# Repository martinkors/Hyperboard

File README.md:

# Hyperboard

A custom development board based on an STM32F479VIT6, used to test custom written drivers.

This board is only a prototype, there are many things that could be improved. It is not advised to follow the design of this board, but instead only use it as a very simplified reference board.

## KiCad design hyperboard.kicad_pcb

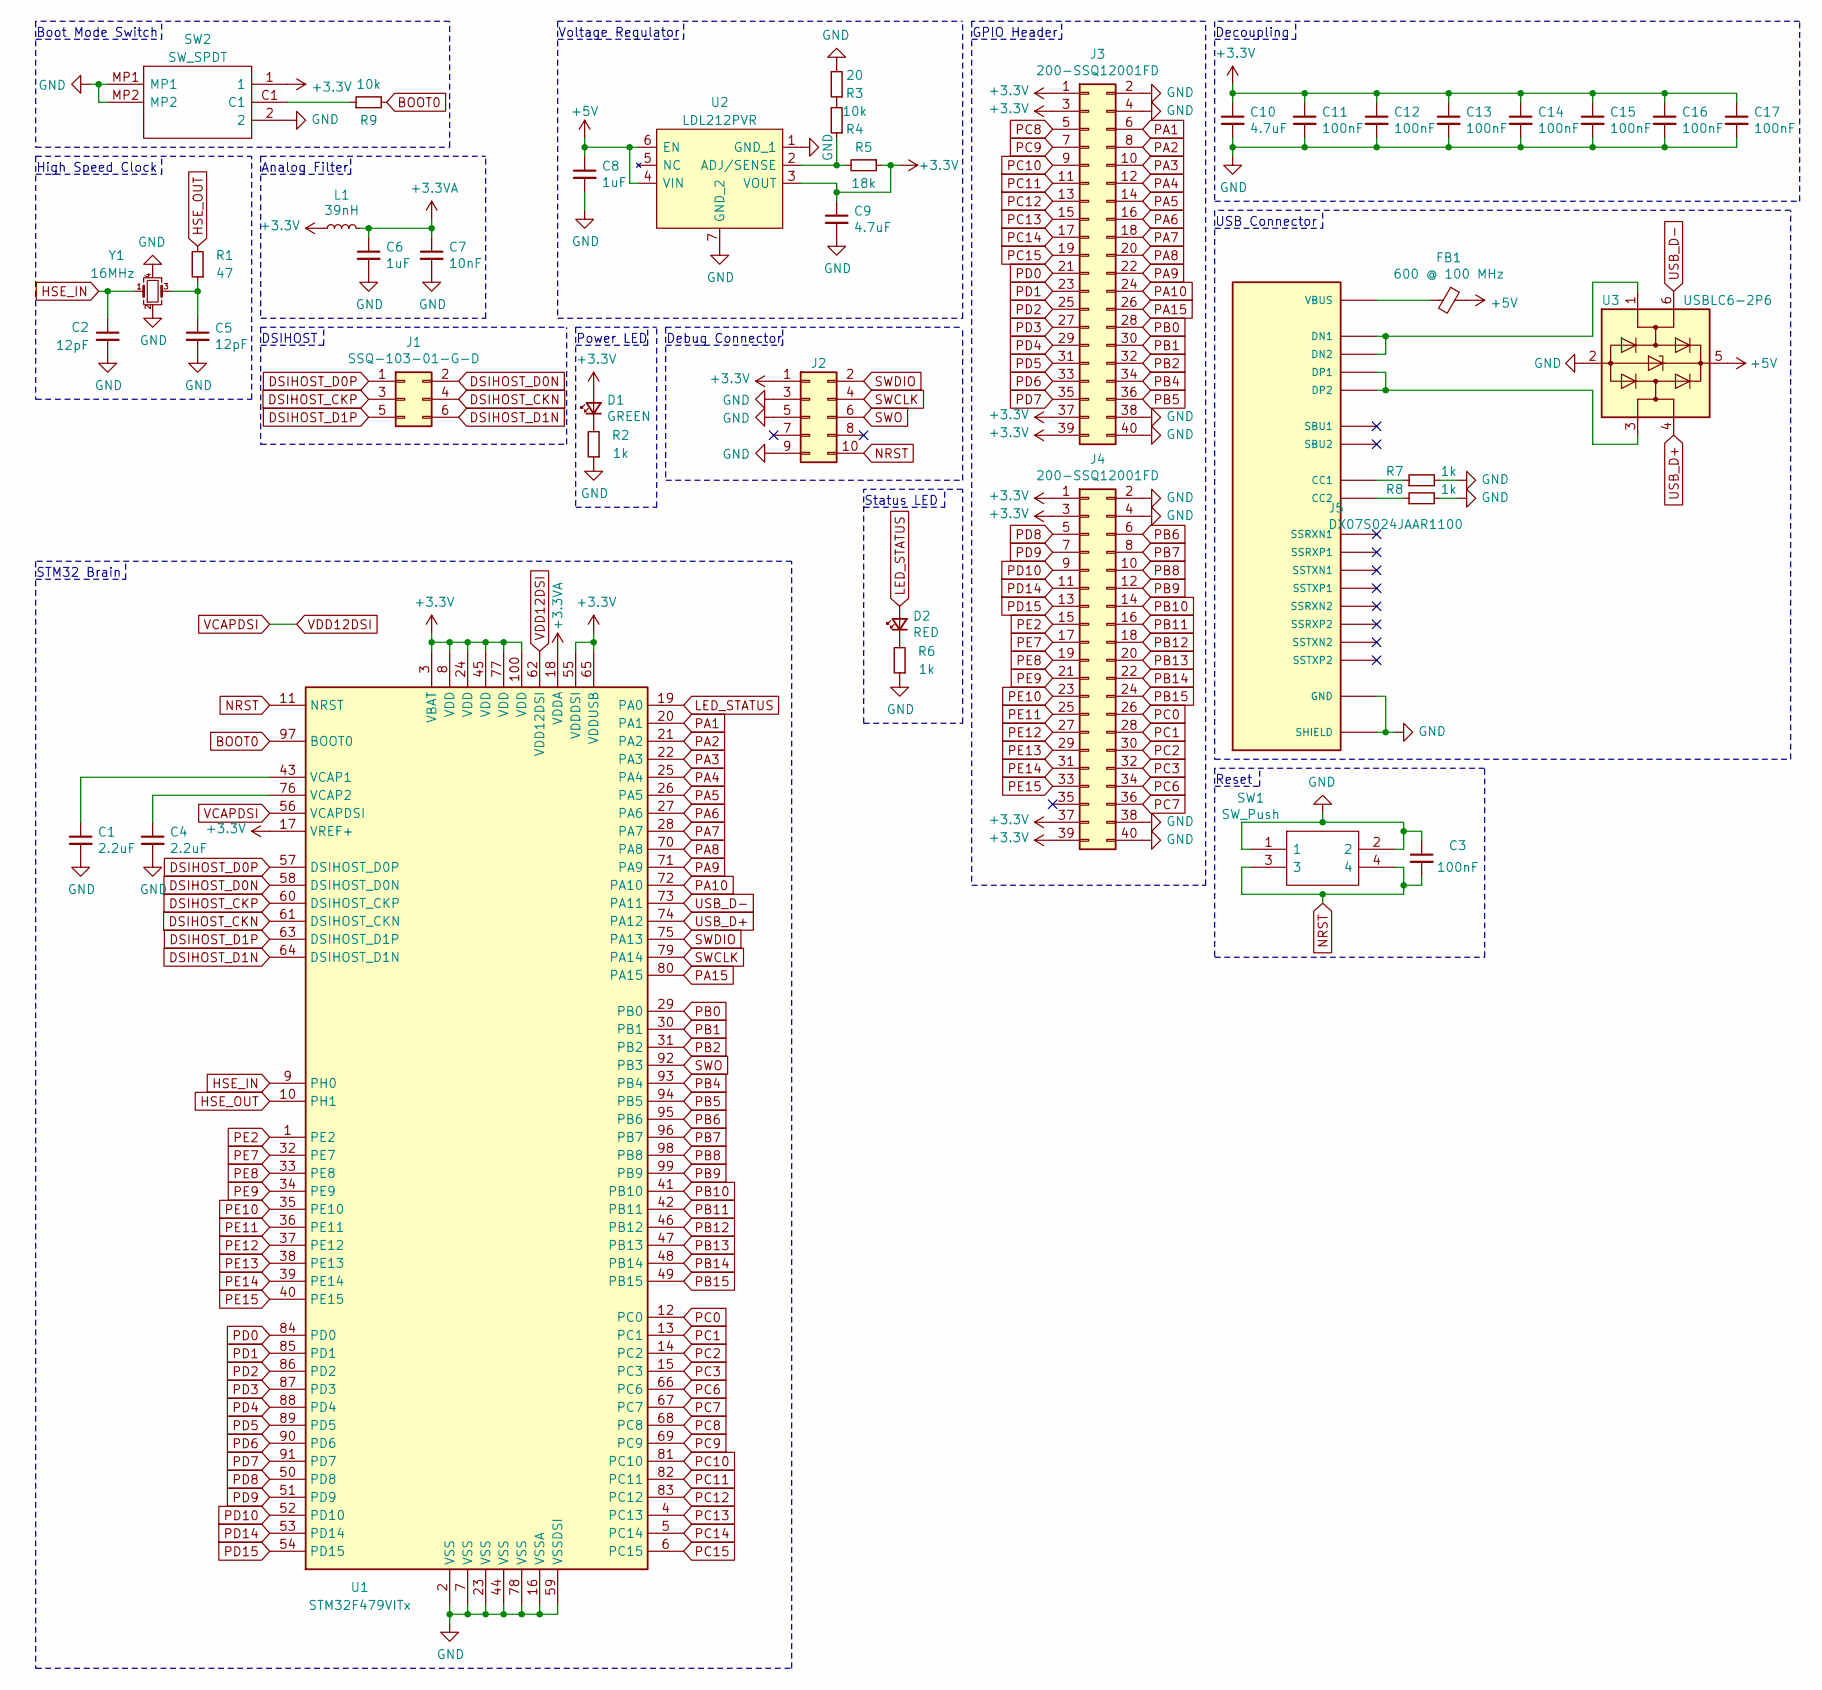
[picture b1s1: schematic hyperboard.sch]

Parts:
C1, C4: 2.2uF; C_0603_1608Metric; Mouser Part Number 187-CL10A225KA8NNNC; LCSC Part # C23630
C2, C5: 12pF; C_0603_1608Metric; Mouser Part Number 187-CL10C120JB81PNC; LCSC Part # C38523
C3, C11, C12, C13, C14, C15, C16, C17: 100nF; C_0402_1005Metric; Mouser Part Number 187-CL05B104KQ5NNNC; LCSC Part # C1525
C6: 1uF; C_0402_1005Metric; Mouser Part Number 187-CL05A105KQ5NNNC; LCSC Part # C52923
C7: 10nF; C_0402_1005Metric; Mouser Part Number 187-CL05B103JO5NNNC; LCSC Part # C15195
C8: 1uF; C_0402_1005Metric; Mouser Part Number 187-CL05A105KQ5NNNC; LCSC Part # C1525
C9: 4.7uF; C_0603_1608Metric; Mouser Part Number 187-CL10A475KQ8NNNC; LCSC Part # C1525
C10: 4.7uF; C_0603_1608Metric; Mouser Part Number 187-CL10A475KQ8NNNC; LCSC Part # C19666
D1: GREEN; LED_0805_2012Metric; Mouser Part Number 710-150080VS75000; LCSC Part # C188728
D2: RED; LED_0805_2012Metric; Mouser Part Number 710-150080RS75000; LCSC Part # C729289
FB1: 600 @ 100 MHz; L_0805_2012Metric; Mouser Part Number 710-742792040; LCSC Part # C1017
J1: SSQ-103-01-G-D; PinSocket_2x03_P2.54mm_Vertical; Mouser Part Number 200-SSQ10301GD
J2: FTSH-105-01-L-DV-K-TR; FTSH10501LDVKTR; Mouser Part Number 200-FTSH10501LDVKTR
J3, J4: 200-SSQ12001FD; SSQ-120-XX-YYY-D; Mouser Part Number 200-SSQ12001FD
J5: DX07S024JAAR1100; PARTREV 1.03; Mouser Part Number 656-DX07S024JAAR1100
L1: 39nH; L_0402_1005Metric; Mouser Part Number 710-7447840139; LCSC Part # C26443
R1: 47; R_0603_1608Metric; Mouser Part Number 667-ERJ-UP3J470V; LCSC Part # C23182
R2, R6, R7, R8: 1k; R_0603_1608Metric; Mouser Part Number 667-ERJ-UP3F1001V; LCSC Part # C21190
R3: 20; R_0603_1608Metric; Mouser Part Number 667-ERJ-UP3F20R0V; LCSC Part # C21190
R4: 10k; R_0603_1608Metric; Mouser Part Number 667-ERJ-UP3F1002V; LCSC Part # C22967
R5: 18k; R_0603_1608Metric; Mouser Part Number 667-ERJ-UP3F1802V; LCSC Part # C25804
R9: 10k; R_0603_1608Metric; Mouser Part Number 667-ERJ-UP3F1002V; LCSC Part # C25804
SW1: SW_Push; SKQGAKE010; Mouser Part Number 688-SKQGAKE010
SW2: SW_SPDT; JSX08001SAQNL; Mouser Part Number 688-SSAJ120100; LCSC Part # C319019
U1: STM32F479VITx; LQFP-100_14x14mm_P0.5mm; Mouser Part Number 511-STM32F479VIT6
U2: LDL212PVR; DFN-6-1EP_2x2mm_P0.65mm_EP1x1.6mm; Mouser Part Number 511-LDL212PVR; LCSC Part # C9056
U3: USBLC6-2P6; SOT-666; Mouser Part Number 511-USBLC6-2P6; LCSC Part # C7519
Y1: 16MHz; Crystal_SMD_3225-4Pin_3.2x2.5mm; Mouser Part Number 344-NX3225SA16MHZT1; LCSC Part # C13738

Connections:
+3.3VA: C6.1, C7.1, L1.2, U1.18 (VDDA)
+3V3: C9.1, C10.1, C11.1, C12.1, C13.1, C14.1, C15.1, C16.1, C17.1, D1.2 (A), J2.1, J3.1, J3.3, J3.37, J3.39, J4.1, J4.3, J4.37, J4.39, L1.1, R5.1, SW2.1, U1.3 (VBAT), U1.8 (VDD), U1.17 (VREF+), U1.24 (VDD), U1.45 (VDD), U1.55 (VDDDSI), U1.65 (VDDUSB), U1.77 (VDD), U1.100 (VDD), U2.3 (VOUT)
+5V: C8.1, FB1.1, U2.4 (VIN), U2.6 (EN), U3.5 (VBUS)
BOOT0: R9.2, U1.97 (BOOT0)
DSIHOST_CKN: J1.4, U1.61 (DSIHOST_CKN)
DSIHOST_CKP: J1.3, U1.60 (DSIHOST_CKP)
DSIHOST_D0N: J1.2, U1.58 (DSIHOST_D0N)
DSIHOST_D0P: J1.1, U1.57 (DSIHOST_D0P)
DSIHOST_D1N: J1.6, U1.64 (DSIHOST_D1N)
DSIHOST_D1P: J1.5, U1.63 (DSIHOST_D1P)
GND: C1.2, C2.2, C3.1, C4.2, C5.2, C6.2, C7.2, C8.2, C9.2, C10.2, C11.2, C12.2, C13.2, C14.2, C15.2, C16.2, C17.2, J2.3, J2.5, J2.9, J3.2, J3.4, J3.38, J3.40, J4.2, J4.4, J4.38, J4.40, J5.1 (SHIELD), J5.2 (SHIELD), J5.3 (SHIELD), J5.4 (SHIELD), J5.A1 (GND), J5.A12 (GND), J5.B1 (GND), J5.B12 (GND), R2.1, R3.2, R6.1, R7.2, R8.2, SW1.1, SW1.2, SW2.2, SW2.MP1, SW2.MP2, U1.2 (VSS), U1.7 (VSS), U1.16 (VSSA), U1.23 (VSS), U1.44 (VSS), U1.59 (VSSDSI), U1.78 (VSS), U2.1 (GND_1), U2.7 (GND_2), U3.2 (GND), Y1.2, Y1.4
HSE_IN: C2.1, U1.9 (PH0), Y1.1
HSE_OUT: R1.2, U1.10 (PH1)
LED_STATUS: D2.2 (A), U1.19 (PA0)
NRST: C3.2, J2.10, SW1.3, SW1.4, U1.11 (NRST)
unnamed: C1.1, U1.43 (VCAP1)
unnamed: C4.1, U1.76 (VCAP2)
unnamed: C5.1, R1.1, Y1.3
unnamed: D1.1 (K), R2.2
unnamed: D2.1 (K), R6.2
unnamed: FB1.2, J5.A4 (VBUS), J5.A9 (VBUS), J5.B4 (VBUS), J5.B9 (VBUS)
unnamed: J5.A5 (CC1), R7.1
unnamed: J5.A6 (DP1), J5.B6 (DP2), U3.3 (I/O2)
unnamed: J5.A7 (DN1), J5.B7 (DN2), U3.1 (I/O1)
unnamed: J5.B5 (CC2), R8.1
unnamed: R3.1, R4.2
unnamed: R4.1, R5.2, U2.2 (ADJ/SENSE)
unnamed: R9.1, SW2.C1
PA1: J3.6, U1.20 (PA1)
PA2: J3.8, U1.21 (PA2)
PA3: J3.10, U1.22 (PA3)
PA4: J3.12, U1.25 (PA4)
PA5: J3.14, U1.26 (PA5)
PA6: J3.16, U1.27 (PA6)
PA7: J3.18, U1.28 (PA7)
PA8: J3.20, U1.70 (PA8)
PA9: J3.22, U1.71 (PA9)
PA10: J3.24, U1.72 (PA10)
PA15: J3.26, U1.80 (PA15)
PB0: J3.28, U1.29 (PB0)
PB1: J3.30, U1.30 (PB1)
PB2: J3.32, U1.31 (PB2)
PB4: J3.34, U1.93 (PB4)
PB5: J3.36, U1.94 (PB5)
PB6: J4.6, U1.95 (PB6)
PB7: J4.8, U1.96 (PB7)
PB8: J4.10, U1.98 (PB8)
PB9: J4.12, U1.99 (PB9)
PB10: J4.14, U1.41 (PB10)
PB11: J4.16, U1.42 (PB11)
PB12: J4.18, U1.46 (PB12)
PB13: J4.20, U1.47 (PB13)
PB14: J4.22, U1.48 (PB14)
PB15: J4.24, U1.49 (PB15)
PC0: J4.26, U1.12 (PC0)
PC1: J4.28, U1.13 (PC1)
PC2: J4.30, U1.14 (PC2)
PC3: J4.32, U1.15 (PC3)
PC6: J4.34, U1.66 (PC6)
PC7: J4.36, U1.67 (PC7)
PC8: J3.5, U1.68 (PC8)
PC9: J3.7, U1.69 (PC9)
PC10: J3.9, U1.81 (PC10)
PC11: J3.11, U1.82 (PC11)
PC12: J3.13, U1.83 (PC12)
PC13: J3.15, U1.4 (PC13)
PC14: J3.17, U1.5 (PC14)
PC15: J3.19, U1.6 (PC15)
PD0: J3.21, U1.84 (PD0)
PD1: J3.23, U1.85 (PD1)
PD2: J3.25, U1.86 (PD2)
PD3: J3.27, U1.87 (PD3)
PD4: J3.29, U1.88 (PD4)
PD5: J3.31, U1.89 (PD5)
PD6: J3.33, U1.90 (PD6)
PD7: J3.35, U1.91 (PD7)
PD8: J4.5, U1.50 (PD8)
PD9: J4.7, U1.51 (PD9)
PD10: J4.9, U1.52 (PD10)
PD14: J4.11, U1.53 (PD14)
PD15: J4.13, U1.54 (PD15)
PE2: J4.15, U1.1 (PE2)
PE7: J4.17, U1.32 (PE7)
PE8: J4.19, U1.33 (PE8)
PE9: J4.21, U1.34 (PE9)
PE10: J4.23, U1.35 (PE10)
PE11: J4.25, U1.36 (PE11)
PE12: J4.27, U1.37 (PE12)
PE13: J4.29, U1.38 (PE13)
PE14: J4.31, U1.39 (PE14)
PE15: J4.33, U1.40 (PE15)
SWCLK: J2.4, U1.79 (PA14)
SWDIO: J2.2, U1.75 (PA13)
SWO: J2.6, U1.92 (PB3)
USB_D+: U1.74 (PA12), U3.4 (I/O2)
USB_D-: U1.73 (PA11), U3.6 (I/O1)
VCAPDSI: U1.56 (VCAPDSI), U1.62 (VDD12DSI)

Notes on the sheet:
USB Connector
Voltage Regulator
Analog Filter
High Speed Clock
Decoupling
Boot Mode Switch
STM32 Brain
GPIO Header
Power LED
DSIHOST
Debug Connector
Status LED
Reset

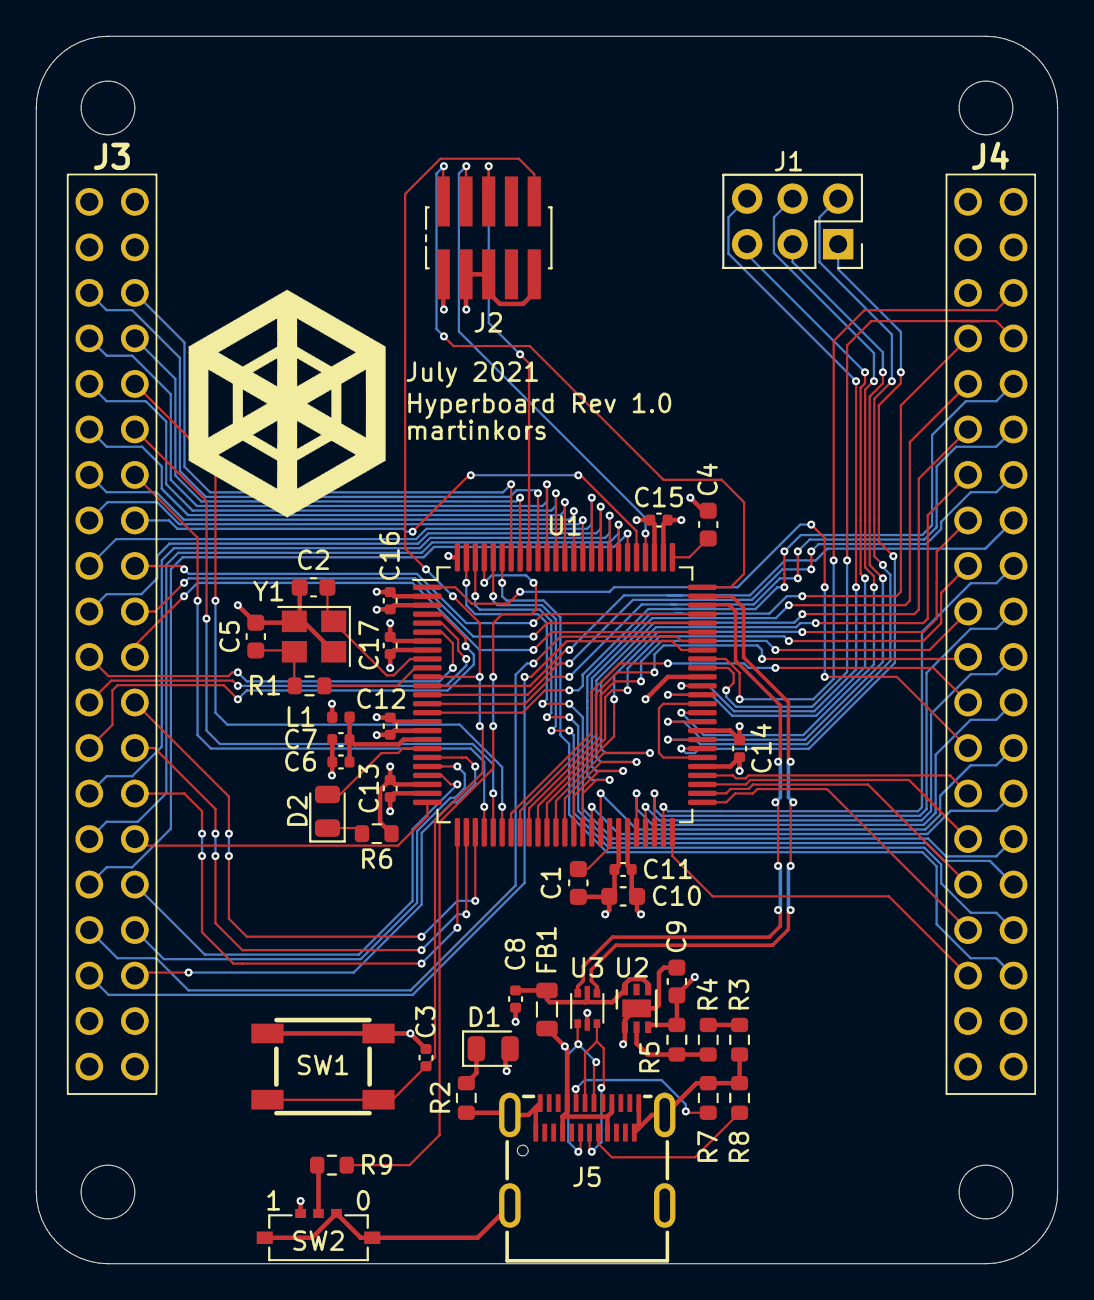
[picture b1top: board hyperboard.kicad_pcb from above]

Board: 4 copper layers, 57.0 x 68.5 mm, 41 parts (0 on the bottom side), 97 nets.

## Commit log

2022-07-05 Added the project files
